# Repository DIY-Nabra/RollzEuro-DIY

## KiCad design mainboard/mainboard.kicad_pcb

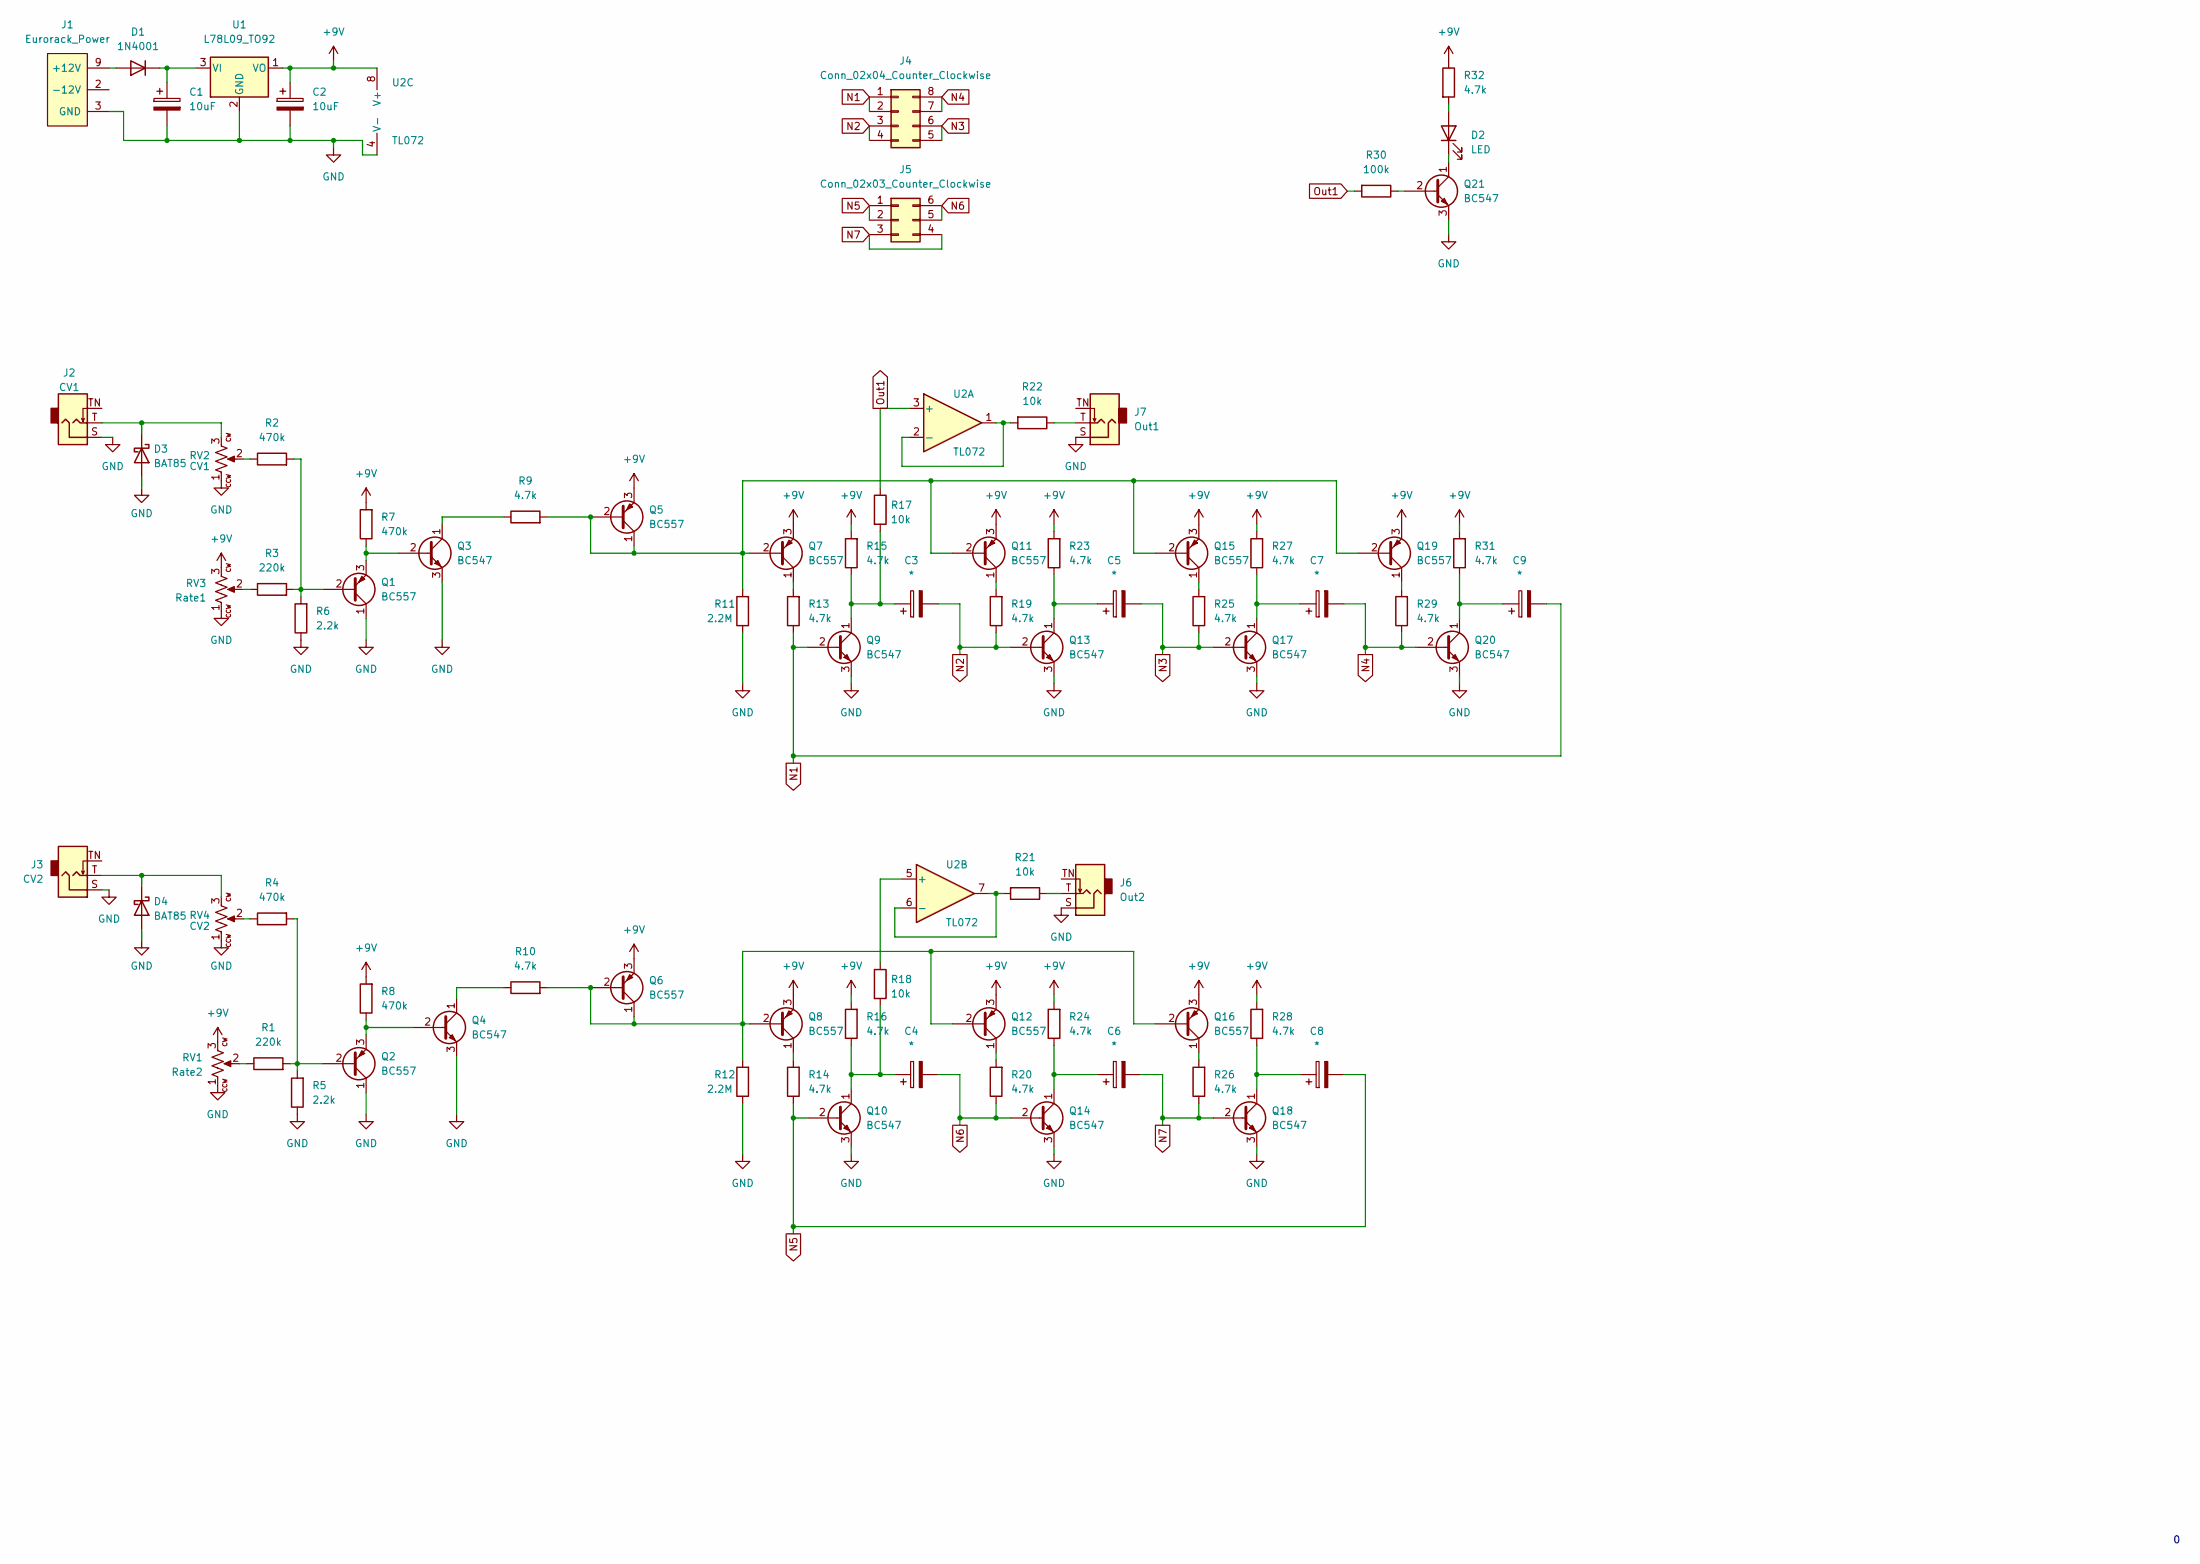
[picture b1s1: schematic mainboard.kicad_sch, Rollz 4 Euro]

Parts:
C1, C2: 10uF; CP_Radial_D5.0mm_P2.50mm
C3, C4, C5, C6, C7, C8, C9: *; CP_Radial_D5.0mm_P2.50mm
D1: 1N4001; D_DO-41_SOD81_P10.16mm_Horizontal
D2: LED; LED_D3.0mm
D3, D4: BAT85; D_DO-35_SOD27_P7.62mm_Horizontal
J1: Eurorack_Power; Eurorack_Power_2x5_Shrouded; mpn 302-S101
J2: CV1; AudioJack_WQP518MA; mpn WQP-WQP518MA
J3: CV2; AudioJack_WQP518MA; mpn WQP-WQP518MA
J4: Conn_02x04_Counter_Clockwise; PinSocket_2x04_P2.54mm_Vertical
J5: Conn_02x03_Counter_Clockwise; PinSocket_2x03_P2.54mm_Vertical
J6: Out2; AudioJack_WQP518MA; mpn WQP-WQP518MA
J7: Out1; AudioJack_WQP518MA; mpn WQP-WQP518MA
Q1, Q2, Q5, Q6, Q7, Q8, Q11, Q12, Q15, Q16, Q19: BC557; TO-92_Inline
Q3, Q4, Q9, Q10, Q13, Q14, Q17, Q18, Q20, Q21: BC547; TO-92_Inline
R1, R3: 220k; R_Axial_DIN0204_L3.6mm_D1.6mm_P7.62mm_Horizontal
R2, R4, R7, R8: 470k; R_Axial_DIN0204_L3.6mm_D1.6mm_P7.62mm_Horizontal
R5, R6: 2.2k; R_Axial_DIN0204_L3.6mm_D1.6mm_P7.62mm_Horizontal
R9, R10, R13, R14, R15, R16, R19, R20, R23, R24, R25, R26, R27, R28, R29, R31, R32: 4.7k; R_Axial_DIN0204_L3.6mm_D1.6mm_P7.62mm_Horizontal
R11, R12: 2.2M; R_Axial_DIN0204_L3.6mm_D1.6mm_P7.62mm_Horizontal
R17, R18, R21, R22: 10k; R_Axial_DIN0204_L3.6mm_D1.6mm_P7.62mm_Horizontal
R30: 100k; R_Axial_DIN0204_L3.6mm_D1.6mm_P7.62mm_Horizontal
RV1: Rate2; Potentiometer_Alpha_R0904N; mpn R0904N-???? L-25KQ/LWS
RV2: CV1; Potentiometer_Alpha_R0904N; mpn R0904N-???? L-25KQ/LWS
RV3: Rate1; Potentiometer_Alpha_R0904N; mpn R0904N-???? L-25KQ/LWS
RV4: CV2; Potentiometer_Alpha_R0904N; mpn R0904N-???? L-25KQ/LWS
U1: L78L09_TO92; TO-92_Inline
U2: TL072; DIP-8_W7.62mm_Socket

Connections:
+9V: C2.1, Q5.3 (E), Q6.3 (E), Q7.3 (E), Q8.3 (E), Q11.3 (E), Q12.3 (E), Q15.3 (E), Q16.3 (E), Q19.3 (E), R7.2, R8.2, R15.2, R16.2, R23.2, R24.2, R27.2, R28.2, R31.2, R32.1, RV1.3, RV3.3, U1.1 (VO), U2.8 (V+)
GND: C1.2, C2.2, D3.2 (A), D4.2 (A), J1.3 (GND), J1.4 (GND), J1.5 (GND), J1.6 (GND), J1.7 (GND), J1.8 (GND), J2.S (Sleeve), J3.S (Sleeve), J6.S (Sleeve), J7.S (Sleeve), Q1.1 (C), Q2.1 (C), Q3.3 (E), Q4.3 (E), Q9.3 (E), Q10.3 (E), Q13.3 (E), Q14.3 (E), Q17.3 (E), Q18.3 (E), Q20.3 (E), Q21.3 (E), R5.1, R6.1, R11.1, R12.1, RV1.1, RV2.1, RV3.1, RV4.1, U1.2 (GND), U2.4 (V-)
N1: C9.2, J4.1, J4.2, Q9.2 (B), R13.1
N2: C3.2, J4.3, J4.4, Q13.2 (B), R19.1
N3: C5.2, J4.5, J4.6, Q17.2 (B), R25.1
N4: C7.2, J4.7, J4.8, Q20.2 (B), R29.1
N5: C8.2, J5.1, J5.2, Q10.2 (B), R14.1
N6: C4.2, J5.5, J5.6, Q14.2 (B), R20.1
N7: C6.2, J5.3, J5.4, Q18.2 (B), R26.1
unnamed: C1.1, D1.1 (K), U1.3 (VI)
unnamed: C3.1, Q9.1 (C), R15.1, R17.2
unnamed: C4.1, Q10.1 (C), R16.1, R18.2
unnamed: C5.1, Q13.1 (C), R23.1
unnamed: C6.1, Q14.1 (C), R24.1
unnamed: C7.1, Q17.1 (C), R27.1
unnamed: C8.1, Q18.1 (C), R28.1
unnamed: C9.1, Q20.1 (C), R31.1
unnamed: D1.2 (A), J1.9 (+12V), J1.10 (+12V)
unnamed: D2.1 (K), Q21.1 (C)
unnamed: D2.2 (A), R32.2
unnamed: J1.1 (-12V), J1.2 (-12V)
unnamed: D3.1 (K), J2.T (Tip), RV2.3
unnamed: D4.1 (K), J3.T (Tip), RV4.3
unnamed: J6.T (Tip), R21.1
unnamed: J7.T (Tip), R22.1
unnamed: Q1.2 (B), R2.2, R3.2, R6.2
unnamed: Q1.3 (E), Q3.2 (B), R7.1
unnamed: Q2.2 (B), R1.2, R4.2, R5.2
unnamed: Q2.3 (E), Q4.2 (B), R8.1
unnamed: Q3.1 (C), R9.1
unnamed: Q4.1 (C), R10.1
unnamed: Q7.1 (C), R13.2
unnamed: Q8.1 (C), R14.2
unnamed: Q11.1 (C), R19.2
unnamed: Q5.1 (C), Q5.2 (B), Q7.2 (B), Q11.2 (B), Q15.2 (B), Q19.2 (B), R9.2, R11.2
unnamed: Q12.1 (C), R20.2
unnamed: Q6.1 (C), Q6.2 (B), Q8.2 (B), Q12.2 (B), Q16.2 (B), R10.2, R12.2
unnamed: Q15.1 (C), R25.2
unnamed: Q16.1 (C), R26.2
unnamed: Q19.1 (C), R29.2
unnamed: Q21.2 (B), R30.1
unnamed: R1.1, RV1.2
unnamed: R2.1, RV2.2
unnamed: R3.1, RV3.2
unnamed: R4.1, RV4.2
unnamed: R18.1, U2.5 (+)
unnamed: R21.2, U2.6 (-), U2.7
unnamed: R22.2, U2.1, U2.2 (-)
Out1: R17.1, R30.2, U2.3 (+)

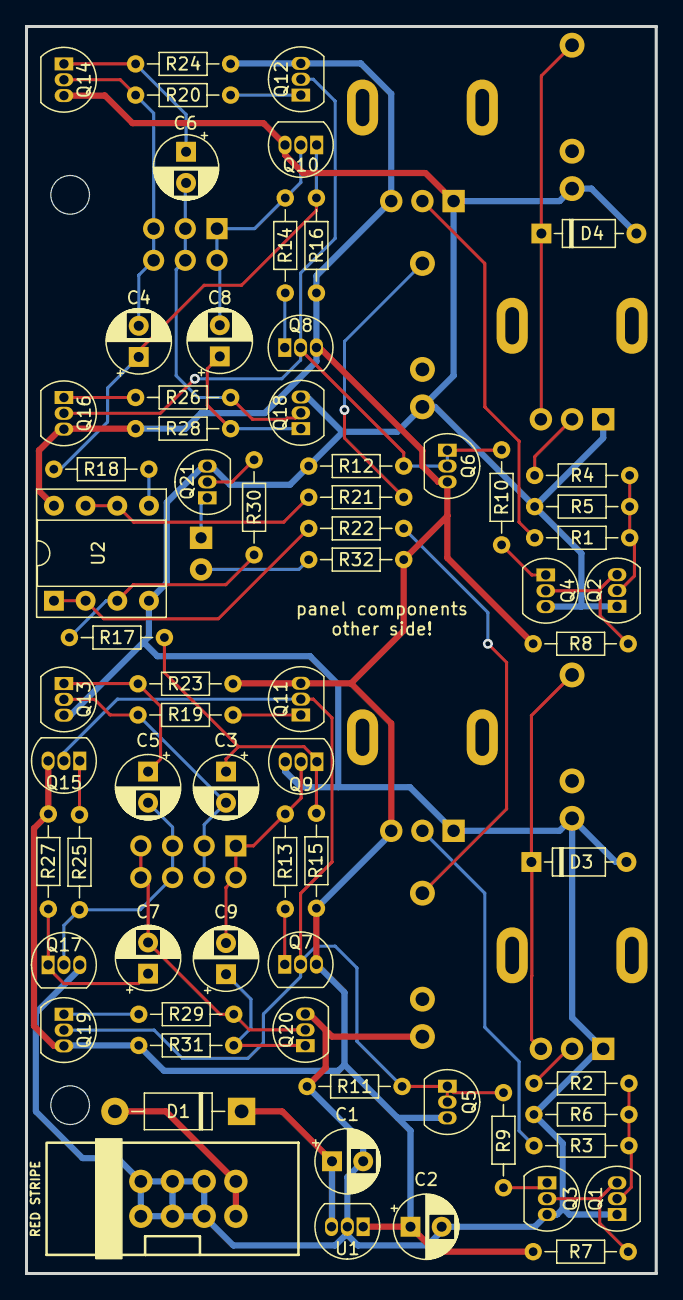
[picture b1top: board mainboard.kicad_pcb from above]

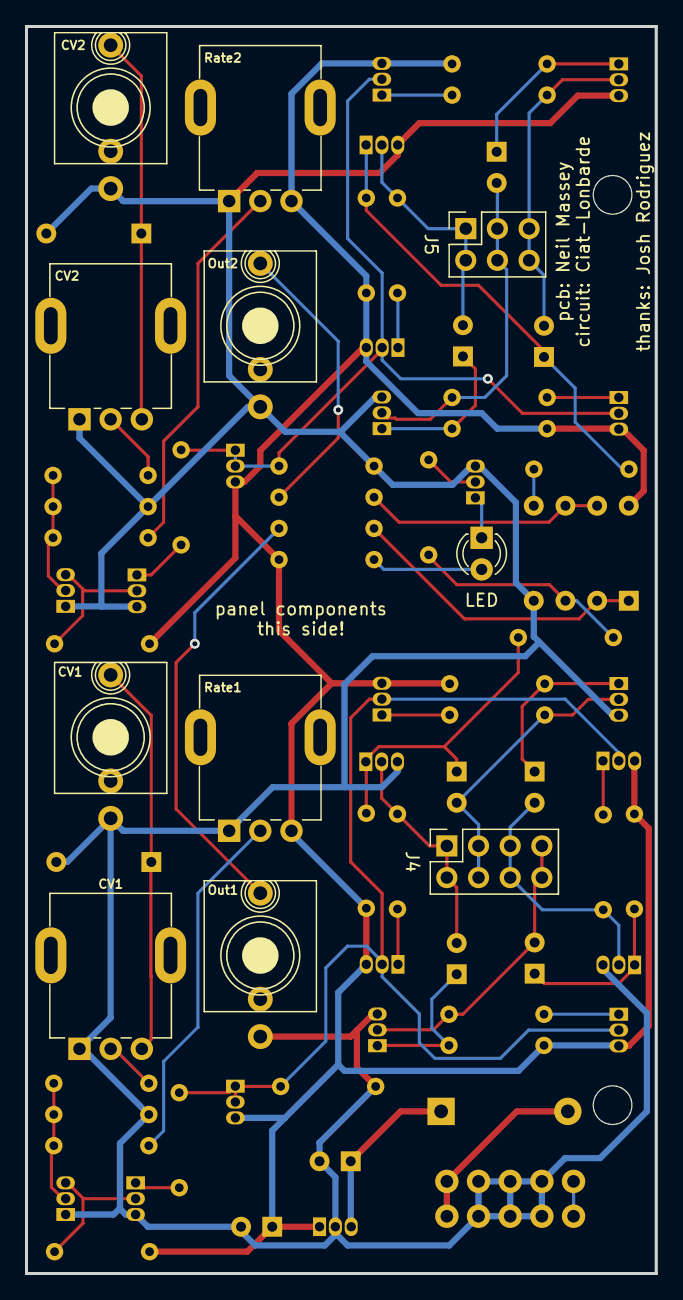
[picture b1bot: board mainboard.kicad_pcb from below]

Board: 2 copper layers, 50.5 x 100.0 mm, 79 parts (11 on the bottom side), 49 nets.

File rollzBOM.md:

# Labrolz Bill of Materials (BOM)

To build just follow the order in the BOM.

When soldering the ICs (U2->U5), solder in the equivalent sockets instead.

Solder the panel components (jacks and pots) last, on the opposite side of the board to the other parts.

| Reference | Quantity | Part | Notes |
|-----------|----------|------|-------|
| R17,R18,R21,R22 | 4 | 10k | |
| R30 | 1 | 100k | |
| R5,R6 | 2 | 2.2k | |
| R1,R3 | 2 | 220k | |
| R11,R12 | 2 | 2.2M | |
| R32,R24,R15,R19,R20,R31,R29,R25,R26,R27,R9,R13,R28,R14,R23,R16,R10 | 17 | 4.7k |
| R2,R4,R7,R8 | 4 | 470k | |
| D1 | 1 | 1N4001 | Reverse voltage protection diode |
| D3,D4 | 2 | BAT85 | Negative voltage protection diodes |
| Q3,Q4,Q9,Q10,Q13,Q14,Q17,Q18,Q20,Q21 | 10 | BC547 | |
| Q1,Q2,Q5,Q6,Q7,Q8,Q11,Q12,Q15,Q16,Q19 | 11 | BC557 | |
| C1,C2 | 2 | 10uF | Power conditioning caps |
| C3,C4,C5,C6,C7,C8,C9 | 7 | Choose your own | Hairy caps, see build note |
| U1 | 1 | L78L09 TO92 | Voltage regulator |
| U2 | 1 | TL072 | or use TL084 |
| J1 | 1 | Eurorack 2x5 shrouded male | |
| D2 | 1 | 3mm LED_D3.0mm | Standard brightness | 
| J4 | 1 | 2x4 female pin header socket | |
| J5 | 1 | 2x3 female pin header socket | |
| J2,J3,J6,J7 | 1 | Thonkiconn 3.5mm mono socket | |
| RV1,RV2,RV3,RV4 | 4 | 10k 9mm potentiometer | |
| IC socket 8 pin | 1 | DIP 8 pin socket | |

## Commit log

2022-08-03 First commit of implementation of CrucFx interpretation of Ciat-Lonbarde Labrolz
2022-08-15 Routing
2022-08-17 Created branch for ver/inver version
2022-08-17 Removed all but PCB from panel
2022-08-17 Attenuator version
2022-08-18 Front panel
2022-08-19 Changes to references
2022-08-25 Trace corrections, panel corrections
2022-08-26 Panel tweak
2022-08-26 Added LICENSE
2022-08-26 Added BOM
2022-08-27 nologo branch and panel
2022-09-03 updated BOM
